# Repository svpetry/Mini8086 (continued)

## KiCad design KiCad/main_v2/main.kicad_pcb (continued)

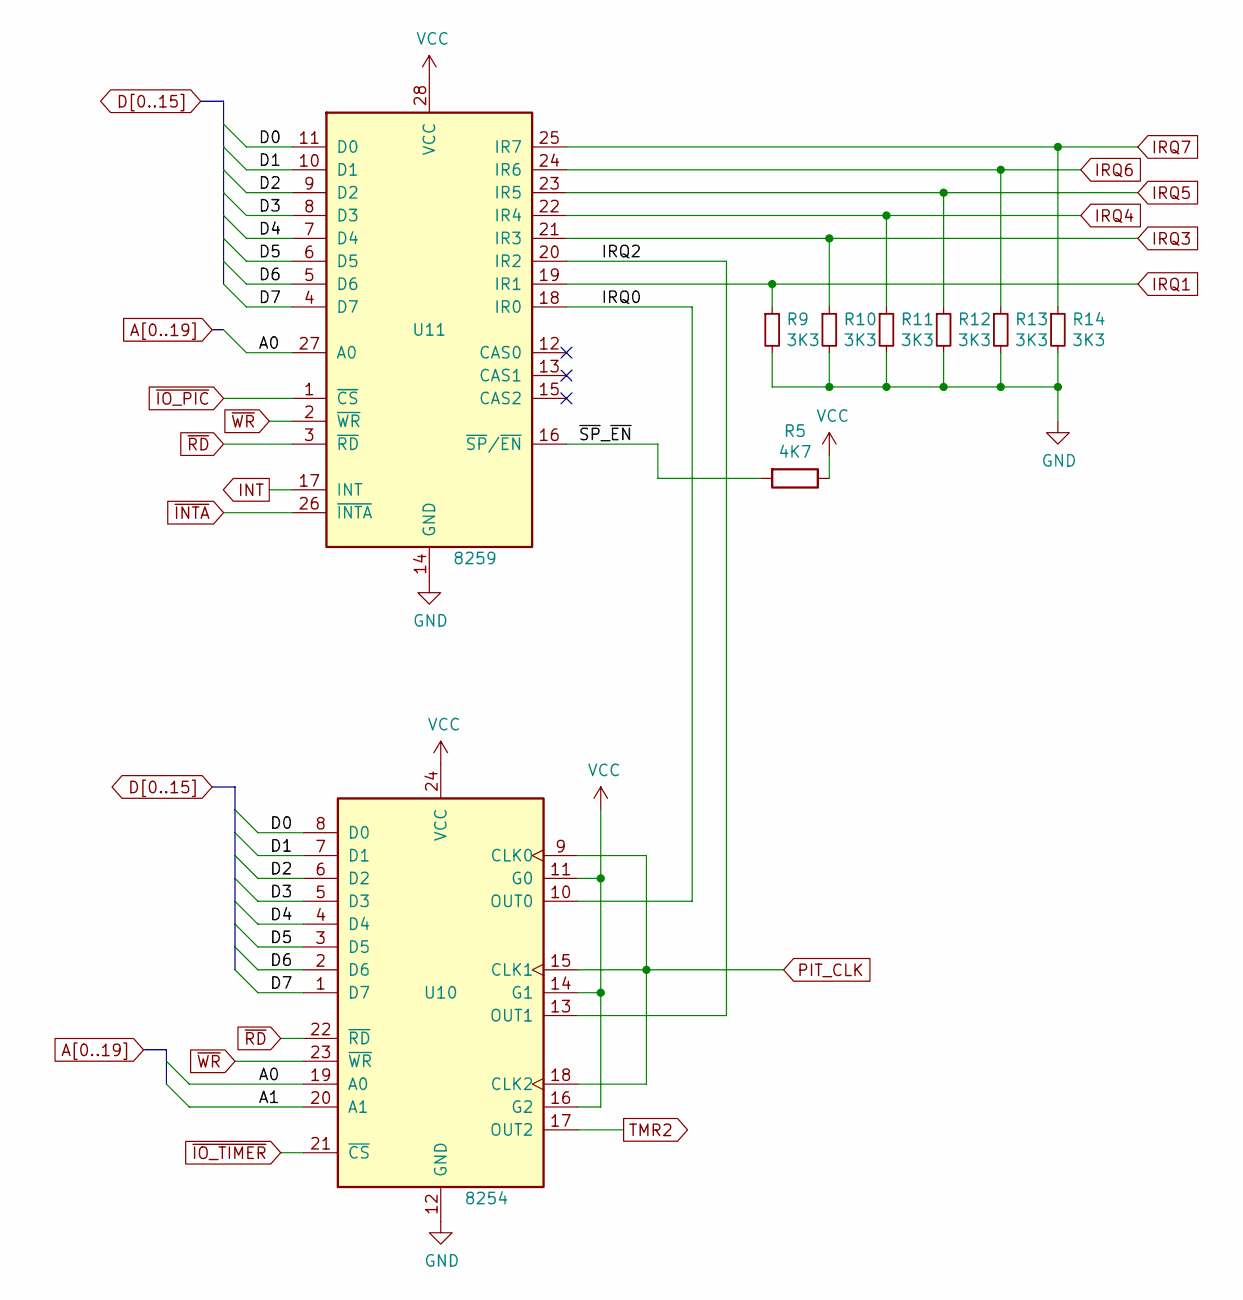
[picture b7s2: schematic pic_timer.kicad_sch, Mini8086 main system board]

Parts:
R5: 4K7; R_1206_3216Metric
R9, R10, R11, R12, R13, R14: 3K3; R_1206_3216Metric
U10: 8254; DIP-24_W15.24mm_Socket_LongPads
U11: 8259; DIP-28_W15.24mm_Socket_LongPads

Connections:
/PIC TIMER/IRQ0: U10.10 (OUT0), U11.18 (IR0)
/PIC TIMER/IRQ2: U10.13 (OUT1), U11.20 (IR2)
/PIC TIMER/~SP~_~EN: R5.2, U11.16 (~SP/~EN)
A0: U10.19 (A0), U11.27 (A0); also elsewhere on the board
A1: U10.20 (A1); also elsewhere on the board
D0: U10.8 (D0), U11.11 (D0); also elsewhere on the board
D1: U10.7 (D1), U11.10 (D1); also elsewhere on the board
D2: U10.6 (D2), U11.9 (D2); also elsewhere on the board
D3: U10.5 (D3), U11.8 (D3); also elsewhere on the board
D4: U10.4 (D4), U11.7 (D4); also elsewhere on the board
D5: U10.3 (D5), U11.6 (D5); also elsewhere on the board
D6: U10.2 (D6), U11.5 (D6); also elsewhere on the board
D7: U10.1 (D7), U11.4 (D7); also elsewhere on the board
GND: R9.2, R10.2, R11.2, R12.2, R13.2, R14.2, U10.12 (GND), U11.14 (GND); also elsewhere on the board
INT: U11.17 (INT); also elsewhere on the board
IRQ1: R9.1, U11.19 (IR1); also elsewhere on the board
IRQ3: R10.1, U11.21 (IR3); also elsewhere on the board
IRQ4: R11.1, U11.22 (IR4); also elsewhere on the board
IRQ5: R12.1, U11.23 (IR5); also elsewhere on the board
IRQ6: R13.1, U11.24 (IR6); also elsewhere on the board
IRQ7: R14.1, U11.25 (IR7); also elsewhere on the board
PIT_CLK: U10.9 (CLK0), U10.15 (CLK1), U10.18 (CLK2); also elsewhere on the board
TMR2: U10.17 (OUT2); also elsewhere on the board
VCC: R5.1, U10.11 (G0), U10.14 (G1), U10.16 (G2), U10.24 (VCC), U11.28 (VCC); also elsewhere on the board
~INTA: U11.26 (~INTA); also elsewhere on the board
~IO_PIC: U11.1 (~CS); also elsewhere on the board
~IO_TIMER: U10.21 (~CS); also elsewhere on the board
~RD: U10.22 (~RD), U11.3 (~RD); also elsewhere on the board
~WR: U10.23 (~WR), U11.2 (~WR); also elsewhere on the board

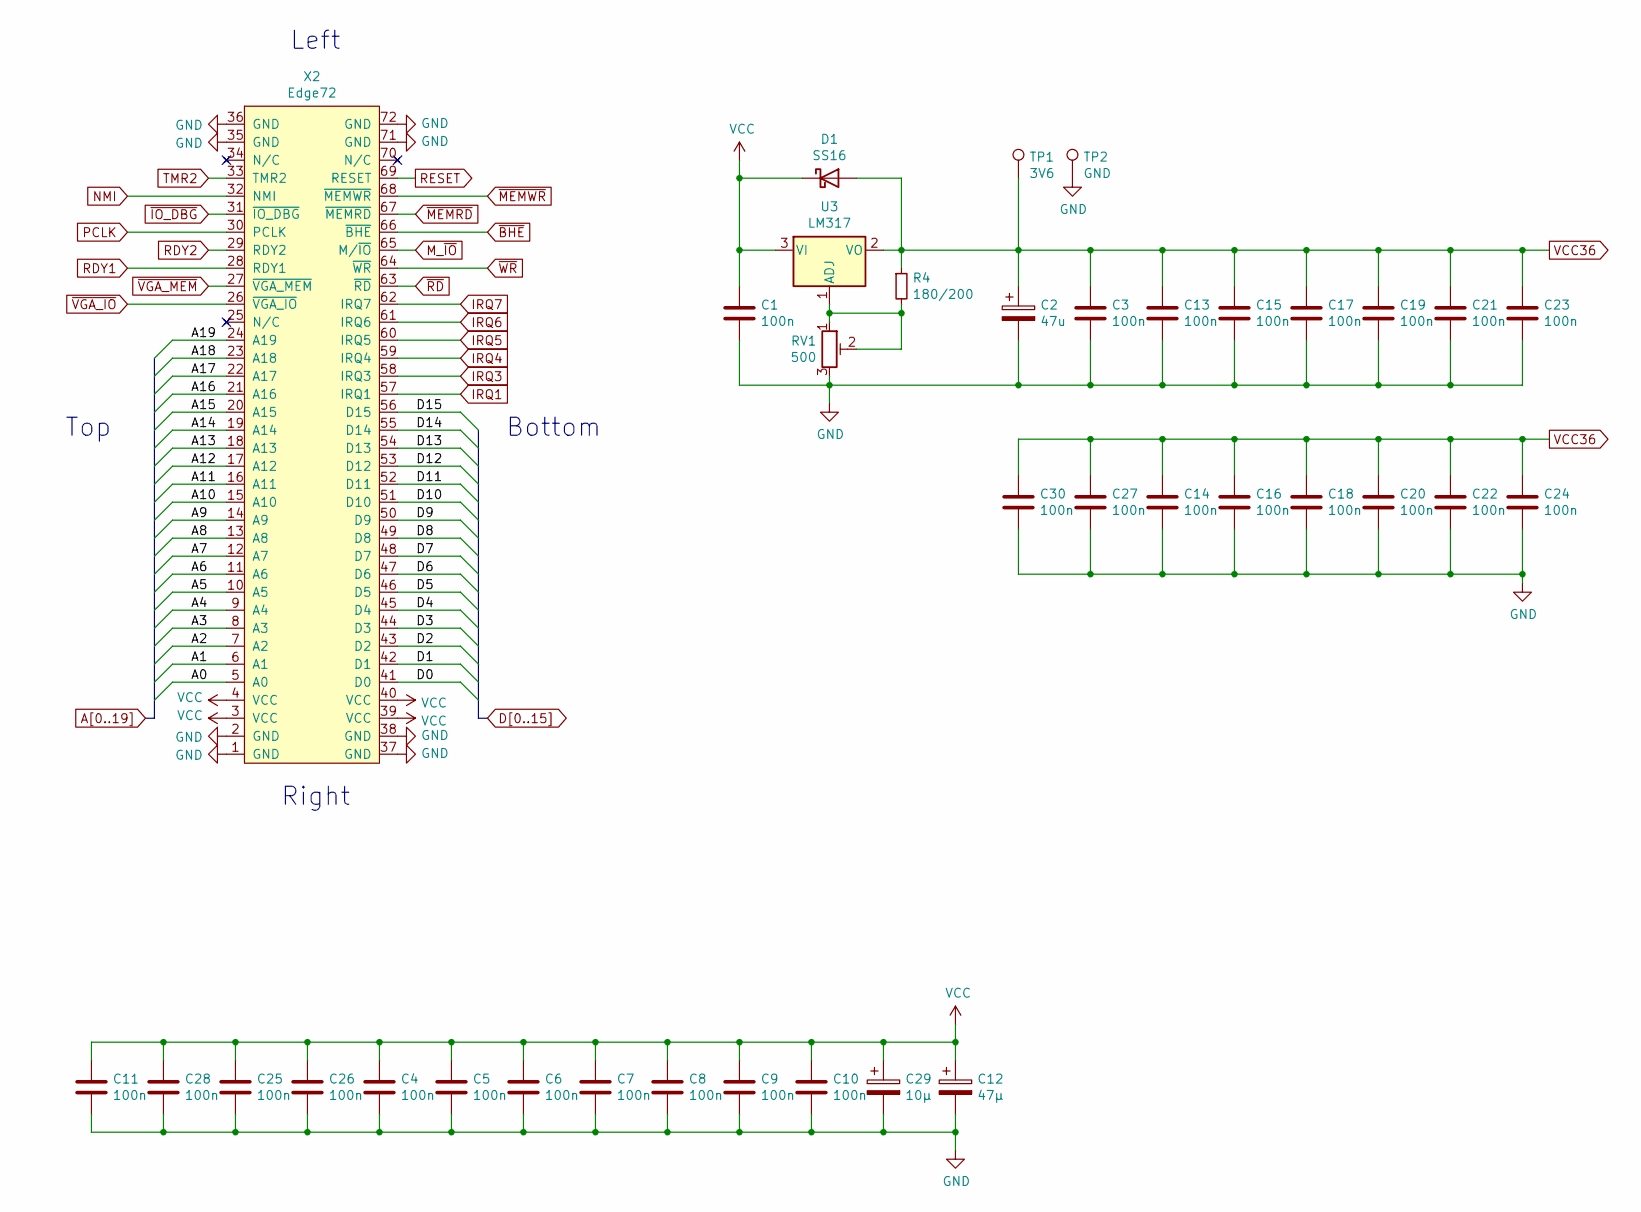
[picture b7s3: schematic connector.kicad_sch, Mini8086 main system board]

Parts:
C1, C3, C4, C5, C6, C7, C8, C9, C10, C11, C13, C14, C15, C16, C17, C18, C19, C20, C21, C22, C23, C24, C25, C26, C27, C28, C30: 100n; C_1206_3216Metric
C2: 47u; CP_Radial_D4.0mm_P2.00mm
C12: 47µ; CP_Radial_D4.0mm_P2.00mm
C29: 10µ; CP_Radial_D4.0mm_P2.00mm
D1: SS16; D_SMA
R4: 180/200; R_1206_3216Metric
RV1: 500; Potentiometer_Runtron_RM-065_Vertical
TP1: 3V6; TestPoint_Pad_D1.5mm
TP2: GND; TestPoint_Pad_D1.5mm
U3: LM317; TO-252-2
X2: Edge72; BUS_72

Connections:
A0: X2.5 (A0); also elsewhere on the board
A1: X2.6 (A1); also elsewhere on the board
A2: X2.7 (A2); also elsewhere on the board
A3: X2.8 (A3); also elsewhere on the board
A4: X2.9 (A4); also elsewhere on the board
A5: X2.10 (A5); also elsewhere on the board
A6: X2.11 (A6); also elsewhere on the board
A7: X2.12 (A7); also elsewhere on the board
A8: X2.13 (A8); also elsewhere on the board
A9: X2.14 (A9); also elsewhere on the board
A10: X2.15 (A10); also elsewhere on the board
A11: X2.16 (A11); also elsewhere on the board
A12: X2.17 (A12); also elsewhere on the board
A13: X2.18 (A13); also elsewhere on the board
A14: X2.19 (A14); also elsewhere on the board
A15: X2.20 (A15); also elsewhere on the board
A16: X2.21 (A16); also elsewhere on the board
A17: X2.22 (A17); also elsewhere on the board
A18: X2.23 (A18); also elsewhere on the board
A19: X2.24 (A19); also elsewhere on the board
D0: X2.41 (D0); also elsewhere on the board
D1: X2.42 (D1); also elsewhere on the board
D2: X2.43 (D2); also elsewhere on the board
D3: X2.44 (D3); also elsewhere on the board
D4: X2.45 (D4); also elsewhere on the board
D5: X2.46 (D5); also elsewhere on the board
D6: X2.47 (D6); also elsewhere on the board
D7: X2.48 (D7); also elsewhere on the board
D8: X2.49 (D8); also elsewhere on the board
D9: X2.50 (D9); also elsewhere on the board
D10: X2.51 (D10); also elsewhere on the board
D11: X2.52 (D11); also elsewhere on the board
D12: X2.53 (D12); also elsewhere on the board
D13: X2.54 (D13); also elsewhere on the board
D14: X2.55 (D14); also elsewhere on the board
D15: X2.56 (D15); also elsewhere on the board
GND: C1.2, C2.2, C3.2, C4.2, C5.2, C6.2, C7.2, C8.2, C9.2, C10.2, C11.2, C12.2, C13.2, C14.2, C15.2, C16.2, C17.2, C18.2, C19.2, C20.2, C21.2, C22.2, C23.2, C24.2, C25.2, C26.2, C27.2, C28.2, C29.2, C30.2, RV1.3, TP2.1, X2.1 (GND), X2.2 (GND), X2.35 (GND), X2.36 (GND), X2.37 (GND), X2.38 (GND), X2.71 (GND), X2.72 (GND); also elsewhere on the board
IRQ1: X2.57 (IRQ1); also elsewhere on the board
IRQ3: X2.58 (IRQ3); also elsewhere on the board
IRQ4: X2.59 (IRQ4); also elsewhere on the board
IRQ5: X2.60 (IRQ5); also elsewhere on the board
IRQ6: X2.61 (IRQ6); also elsewhere on the board
IRQ7: X2.62 (IRQ7); also elsewhere on the board
M_~IO: X2.65 (M/~IO); also elsewhere on the board
NMI: X2.32 (NMI); also elsewhere on the board
unnamed: R4.2, RV1.1, RV1.2, U3.1 (ADJ)
PCLK: X2.30 (PCLK); also elsewhere on the board
RDY1: X2.28 (RDY1); also elsewhere on the board
RDY2: X2.29 (RDY2); also elsewhere on the board
RESET: X2.69 (RESET); also elsewhere on the board
TMR2: X2.33 (TMR2); also elsewhere on the board
VCC: C1.1, C4.1, C5.1, C6.1, C7.1, C8.1, C9.1, C10.1, C11.1, C12.1, C25.1, C26.1, C28.1, C29.1, D1.1 (K), U3.3 (VI), X2.3 (VCC), X2.4 (VCC), X2.39 (VCC), X2.40 (VCC); also elsewhere on the board
VCC36: C2.1, C3.1, C13.1, C14.1, C15.1, C16.1, C17.1, C18.1, C19.1, C20.1, C21.1, C22.1, C23.1, C24.1, C27.1, C30.1, D1.2 (A), R4.1, TP1.1, U3.2 (VO); also elsewhere on the board
~BHE: X2.66 (~BHE); also elsewhere on the board
~IO_DBG: X2.31 (~IO_DBG); also elsewhere on the board
~MEMRD: X2.67 (~MEMRD); also elsewhere on the board
~MEMWR: X2.68 (~MEMWR); also elsewhere on the board
~RD: X2.63 (~RD); also elsewhere on the board
~VGA_IO: X2.26 (~VGA_IO); also elsewhere on the board
~VGA_MEM: X2.27 (~VGA_MEM); also elsewhere on the board
~WR: X2.64 (~WR); also elsewhere on the board

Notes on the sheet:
Top
Right
Left
Bottom

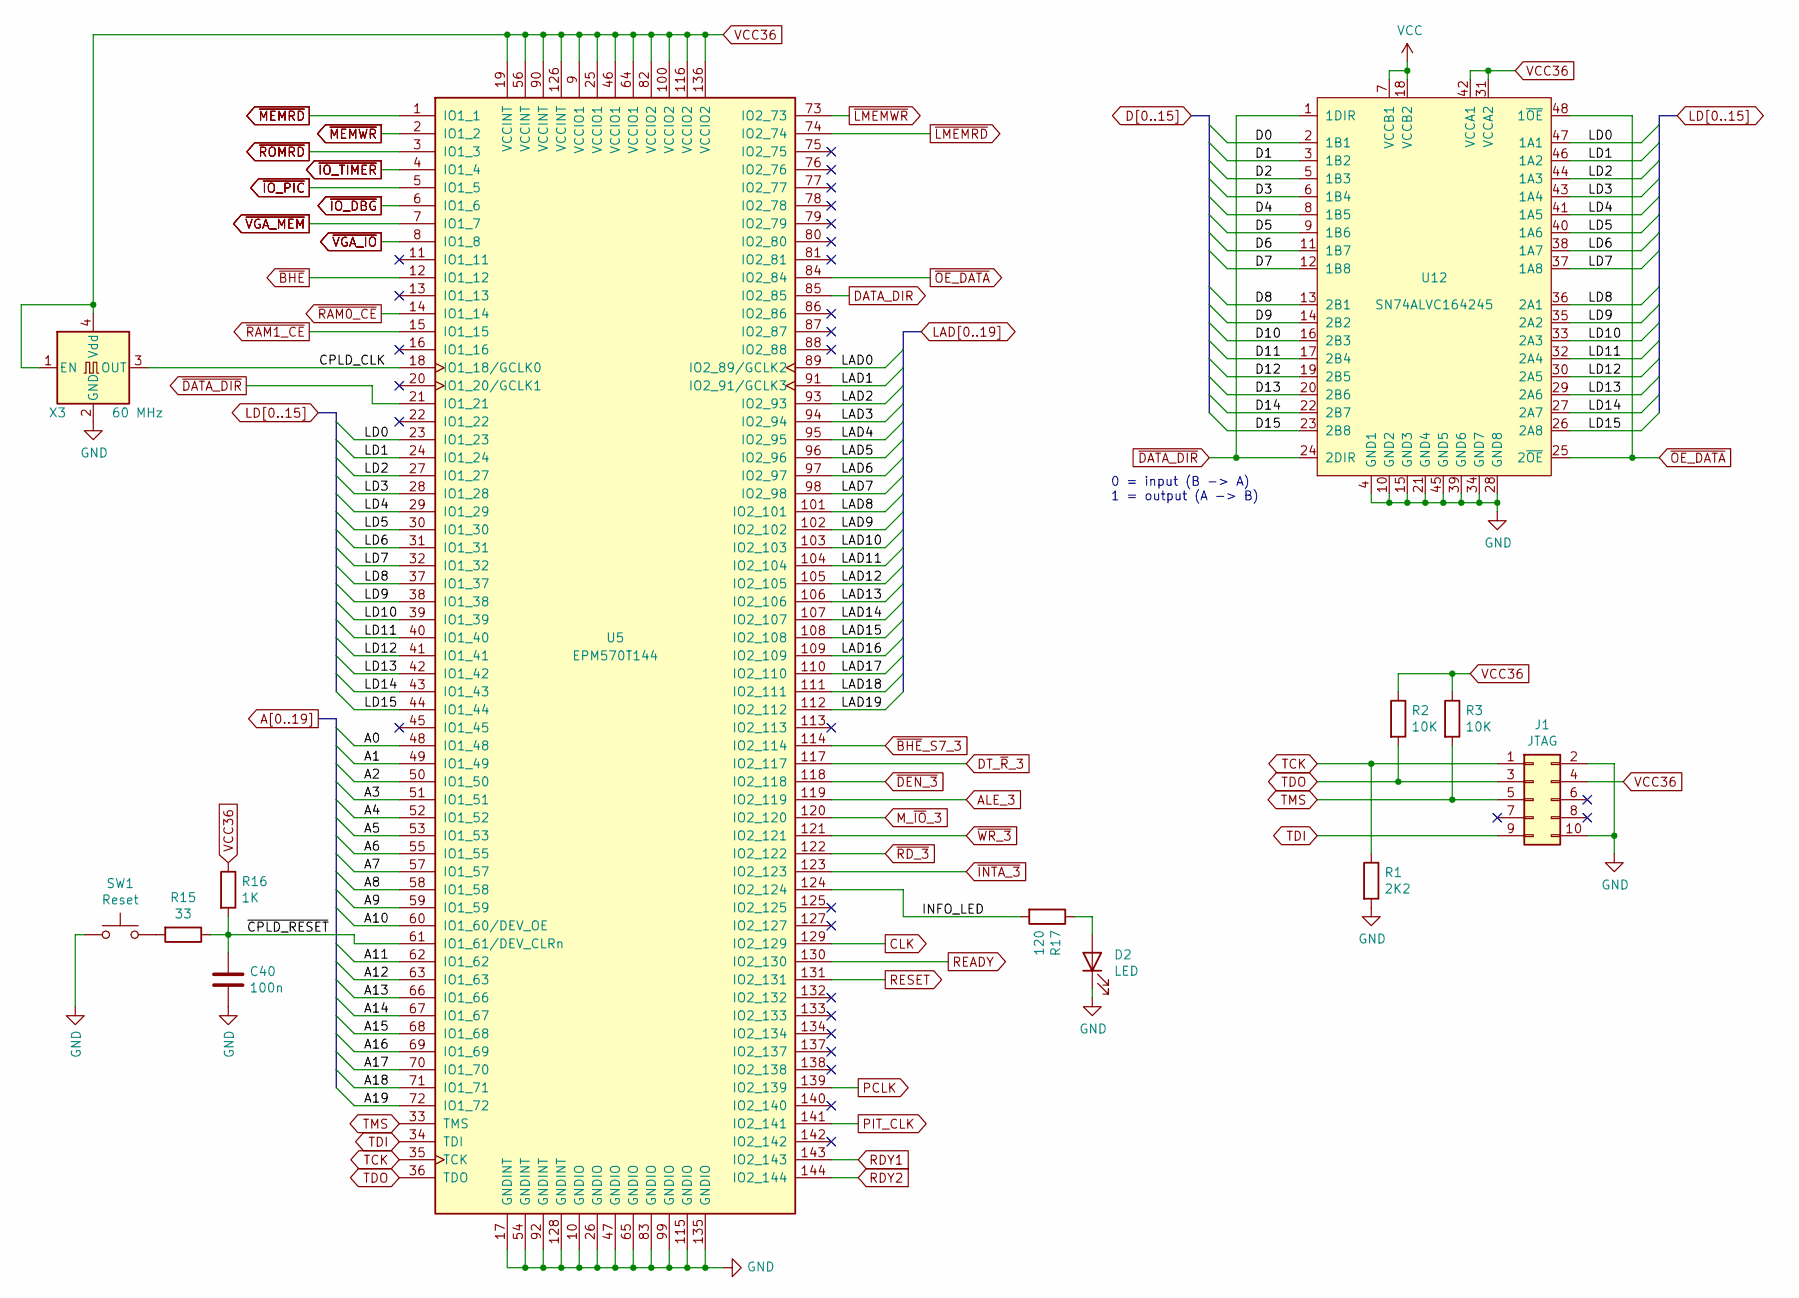
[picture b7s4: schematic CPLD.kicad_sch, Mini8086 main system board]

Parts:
C40: 100n; C_1206_3216Metric
D2: LED; LED_0805_2012Metric_Castellated
J1: JTAG; IDC-Header_2x05_P2.54mm_Vertical
R1: 2K2; R_1206_3216Metric
R2, R3: 10K; R_1206_3216Metric
R15: 33; R_1206_3216Metric
R16: 1K; R_1206_3216Metric
R17: 120; R_0805_2012Metric
SW1: Reset; SW_SPST_CK_RS282G05A3
U5: EPM570T144; LQFP-144_20x20mm_P0.5mm
U12: SN74ALVC164245; SSOP-48_7.5x15.9mm_P0.635mm
X3: 60 MHz; Oscillator_SMD_Abracon_ASV-4Pin_7.0x5.1mm

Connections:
/CPLD/CPLD_CLK: U5.18 (IO1_18/GCLK0), X3.3 (OUT)
/CPLD/INFO_LED: R17.2, U5.124 (IO2_124)
/CPLD/~CPLD_RESET: C40.1, R15.1, R16.2, U5.61 (IO1_61/DEV_CLRn)
A0: U5.48 (IO1_48); also elsewhere on the board
A1: U5.49 (IO1_49); also elsewhere on the board
A2: U5.50 (IO1_50); also elsewhere on the board
A3: U5.51 (IO1_51); also elsewhere on the board
A4: U5.52 (IO1_52); also elsewhere on the board
A5: U5.53 (IO1_53); also elsewhere on the board
A6: U5.55 (IO1_55); also elsewhere on the board
A7: U5.57 (IO1_57); also elsewhere on the board
A8: U5.58 (IO1_58); also elsewhere on the board
A9: U5.59 (IO1_59); also elsewhere on the board
A10: U5.60 (IO1_60/DEV_OE); also elsewhere on the board
A11: U5.62 (IO1_62); also elsewhere on the board
A12: U5.63 (IO1_63); also elsewhere on the board
A13: U5.66 (IO1_66); also elsewhere on the board
A14: U5.67 (IO1_67); also elsewhere on the board
A15: U5.68 (IO1_68); also elsewhere on the board
A16: U5.69 (IO1_69); also elsewhere on the board
A17: U5.70 (IO1_70); also elsewhere on the board
A18: U5.71 (IO1_71); also elsewhere on the board
A19: U5.72 (IO1_72); also elsewhere on the board
ALE_3: U5.119 (IO2_119); also elsewhere on the board
CLK: U5.129 (IO2_129); also elsewhere on the board
D0: U12.2 (1B1); also elsewhere on the board
D1: U12.3 (1B2); also elsewhere on the board
D2: U12.5 (1B3); also elsewhere on the board
D3: U12.6 (1B4); also elsewhere on the board
D4: U12.8 (1B5); also elsewhere on the board
D5: U12.9 (1B6); also elsewhere on the board
D6: U12.11 (1B7); also elsewhere on the board
D7: U12.12 (1B8); also elsewhere on the board
D8: U12.13 (2B1); also elsewhere on the board
D9: U12.14 (2B2); also elsewhere on the board
D10: U12.16 (2B3); also elsewhere on the board
D11: U12.17 (2B4); also elsewhere on the board
D12: U12.19 (2B5); also elsewhere on the board
D13: U12.20 (2B6); also elsewhere on the board
D14: U12.22 (2B7); also elsewhere on the board
D15: U12.23 (2B8); also elsewhere on the board
DATA_DIR: U5.85 (IO2_85); also elsewhere on the board
DT_~R~_3: U5.117 (IO2_117); also elsewhere on the board
GND: C40.2, D2.1 (K), J1.2, J1.10, R1.2, SW1.1, U5.10 (GNDIO), U5.17 (GNDINT), U5.26 (GNDIO), U5.47 (GNDIO), U5.54 (GNDINT), U5.65 (GNDIO), U5.83 (GNDIO), U5.92 (GNDINT), U5.99 (GNDIO), U5.115 (GNDIO), U5.128 (GNDINT), U5.135 (GNDIO), U12.4 (GND1), U12.10 (GND2), U12.15 (GND3), U12.21 (GND4), U12.28 (GND8), U12.34 (GND7), U12.39 (GND6), U12.45 (GND5), X3.2 (GND); also elsewhere on the board
LAD0: U5.89 (IO2_89/GCLK2); also elsewhere on the board
LAD1: U5.91 (IO2_91/GCLK3); also elsewhere on the board
LAD2: U5.93 (IO2_93); also elsewhere on the board
LAD3: U5.94 (IO2_94); also elsewhere on the board
LAD4: U5.95 (IO2_95); also elsewhere on the board
LAD5: U5.96 (IO2_96); also elsewhere on the board
LAD6: U5.97 (IO2_97); also elsewhere on the board
LAD7: U5.98 (IO2_98); also elsewhere on the board
LAD8: U5.101 (IO2_101); also elsewhere on the board
LAD9: U5.102 (IO2_102); also elsewhere on the board
LAD10: U5.103 (IO2_103); also elsewhere on the board
LAD11: U5.104 (IO2_104); also elsewhere on the board
LAD12: U5.105 (IO2_105); also elsewhere on the board
LAD13: U5.106 (IO2_106); also elsewhere on the board
LAD14: U5.107 (IO2_107); also elsewhere on the board
LAD15: U5.108 (IO2_108); also elsewhere on the board
LAD16: U5.109 (IO2_109); also elsewhere on the board
LAD17: U5.110 (IO2_110); also elsewhere on the board
LAD18: U5.111 (IO2_111); also elsewhere on the board
LAD19: U5.112 (IO2_112); also elsewhere on the board
LD0: U5.23 (IO1_23), U12.47 (1A1); also elsewhere on the board
LD1: U5.24 (IO1_24), U12.46 (1A2); also elsewhere on the board
LD2: U5.27 (IO1_27), U12.44 (1A3); also elsewhere on the board
LD3: U5.28 (IO1_28), U12.43 (1A4); also elsewhere on the board
LD4: U5.29 (IO1_29), U12.41 (1A5); also elsewhere on the board
LD5: U5.30 (IO1_30), U12.40 (1A6); also elsewhere on the board
LD6: U5.31 (IO1_31), U12.38 (1A7); also elsewhere on the board
LD7: U5.32 (IO1_32), U12.37 (1A8); also elsewhere on the board
LD8: U5.37 (IO1_37), U12.36 (2A1); also elsewhere on the board
LD9: U5.38 (IO1_38), U12.35 (2A2); also elsewhere on the board
LD10: U5.39 (IO1_39), U12.33 (2A3); also elsewhere on the board
LD11: U5.40 (IO1_40), U12.32 (2A4); also elsewhere on the board
LD12: U5.41 (IO1_41), U12.30 (2A5); also elsewhere on the board
LD13: U5.42 (IO1_42), U12.29 (2A6); also elsewhere on the board
LD14: U5.43 (IO1_43), U12.27 (2A7); also elsewhere on the board
LD15: U5.44 (IO1_44), U12.26 (2A8); also elsewhere on the board
M_~IO~_3: U5.120 (IO2_120); also elsewhere on the board
unnamed: D2.2 (A), R17.1
unnamed: R15.2, SW1.2
PCLK: U5.139 (IO2_139); also elsewhere on the board
PIT_CLK: U5.141 (IO2_141); also elsewhere on the board
RDY1: U5.143 (IO2_143); also elsewhere on the board
RDY2: U5.144 (IO2_144); also elsewhere on the board
READY: U5.130 (IO2_130); also elsewhere on the board
RESET: U5.131 (IO2_131); also elsewhere on the board
TCK: J1.1, R1.1, U5.35 (TCK)
TDI: J1.9, U5.34 (TDI)
TDO: J1.3, R2.2, U5.36 (TDO)
TMS: J1.5, R3.2, U5.33 (TMS)
VCC: U12.7 (VCCB1), U12.18 (VCCB2); also elsewhere on the board
VCC36: J1.4, R2.1, R3.1, R16.1, U5.9 (VCCIO1), U5.19 (VCCINT), U5.25 (VCCIO1), U5.46 (VCCIO1), U5.56 (VCCINT), U5.64 (VCCIO1), U5.82 (VCCIO2), U5.90 (VCCINT), U5.100 (VCCIO2), U5.116 (VCCIO2), U5.126 (VCCINT), U5.136 (VCCIO2), U12.31 (VCCA2), U12.42 (VCCA1), X3.1 (EN), X3.4 (Vdd); also elsewhere on the board
~BHE: U5.12 (IO1_12); also elsewhere on the board
~BHE~_S7_3: U5.114 (IO2_114); also elsewhere on the board
~DATA_DIR: U5.21 (IO1_21), U12.1 (1DIR), U12.24 (2DIR)
~DEN_3: U5.118 (IO2_118); also elsewhere on the board
~INTA_3: U5.123 (IO2_123); also elsewhere on the board
~IO_DBG: U5.6 (IO1_6); also elsewhere on the board
~IO_PIC: U5.5 (IO1_5); also elsewhere on the board
~IO_TIMER: U5.4 (IO1_4); also elsewhere on the board
~LMEMRD: U5.74 (IO2_74); also elsewhere on the board
~LMEMWR: U5.73 (IO2_73); also elsewhere on the board
~MEMRD: U5.1 (IO1_1); also elsewhere on the board
~MEMWR: U5.2 (IO1_2); also elsewhere on the board
~OE_DATA: U5.84 (IO2_84), U12.25 (2~OE), U12.48 (1~OE)
~RAM0_CE: U5.14 (IO1_14); also elsewhere on the board
~RAM1_CE: U5.15 (IO1_15); also elsewhere on the board
~RD_3: U5.122 (IO2_122); also elsewhere on the board
~ROMRD: U5.3 (IO1_3); also elsewhere on the board
~VGA_IO: U5.8 (IO1_8); also elsewhere on the board
~VGA_MEM: U5.7 (IO1_7); also elsewhere on the board
~WR_3: U5.121 (IO2_121); also elsewhere on the board

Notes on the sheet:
0 = input (B -> A) 1 = output (A -> B)

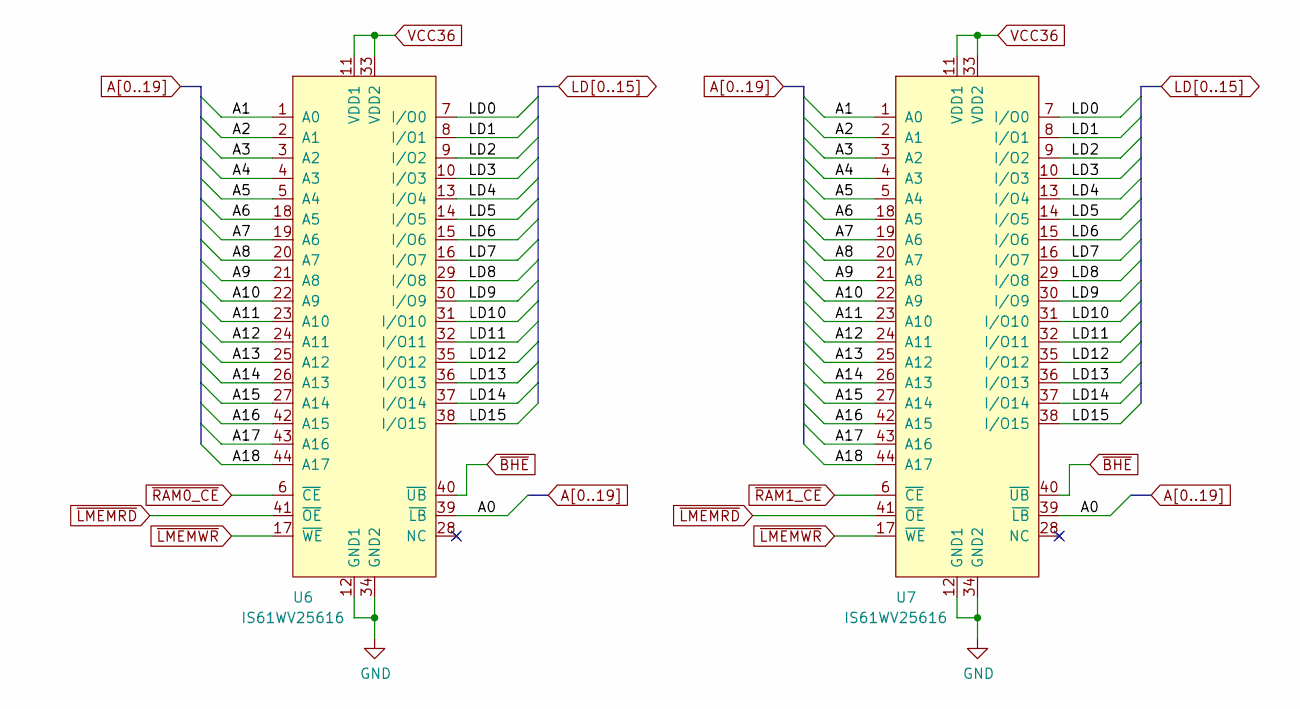
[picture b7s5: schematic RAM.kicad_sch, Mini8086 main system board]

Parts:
U6, U7: IS61WV25616; TSOP-II-44_10.16x18.41mm_P0.8mm

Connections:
A0: U6.39 (~LB), U7.39 (~LB); also elsewhere on the board
A1: U6.1 (A0), U7.1 (A0); also elsewhere on the board
A2: U6.2 (A1), U7.2 (A1); also elsewhere on the board
A3: U6.3 (A2), U7.3 (A2); also elsewhere on the board
A4: U6.4 (A3), U7.4 (A3); also elsewhere on the board
A5: U6.5 (A4), U7.5 (A4); also elsewhere on the board
A6: U6.18 (A5), U7.18 (A5); also elsewhere on the board
A7: U6.19 (A6), U7.19 (A6); also elsewhere on the board
A8: U6.20 (A7), U7.20 (A7); also elsewhere on the board
A9: U6.21 (A8), U7.21 (A8); also elsewhere on the board
A10: U6.22 (A9), U7.22 (A9); also elsewhere on the board
A11: U6.23 (A10), U7.23 (A10); also elsewhere on the board
A12: U6.24 (A11), U7.24 (A11); also elsewhere on the board
A13: U6.25 (A12), U7.25 (A12); also elsewhere on the board
A14: U6.26 (A13), U7.26 (A13); also elsewhere on the board
A15: U6.27 (A14), U7.27 (A14); also elsewhere on the board
A16: U6.42 (A15), U7.42 (A15); also elsewhere on the board
A17: U6.43 (A16), U7.43 (A16); also elsewhere on the board
A18: U6.44 (A17), U7.44 (A17); also elsewhere on the board
GND: U6.12 (GND1), U6.34 (GND2), U7.12 (GND1), U7.34 (GND2); also elsewhere on the board
LD0: U6.7 (I/O0), U7.7 (I/O0); also elsewhere on the board
LD1: U6.8 (I/O1), U7.8 (I/O1); also elsewhere on the board
LD2: U6.9 (I/O2), U7.9 (I/O2); also elsewhere on the board
LD3: U6.10 (I/O3), U7.10 (I/O3); also elsewhere on the board
LD4: U6.13 (I/O4), U7.13 (I/O4); also elsewhere on the board
LD5: U6.14 (I/O5), U7.14 (I/O5); also elsewhere on the board
LD6: U6.15 (I/O6), U7.15 (I/O6); also elsewhere on the board
LD7: U6.16 (I/O7), U7.16 (I/O7); also elsewhere on the board
LD8: U6.29 (I/O8), U7.29 (I/O8); also elsewhere on the board
LD9: U6.30 (I/O9), U7.30 (I/O9); also elsewhere on the board
LD10: U6.31 (I/O10), U7.31 (I/O10); also elsewhere on the board
LD11: U6.32 (I/O11), U7.32 (I/O11); also elsewhere on the board
LD12: U6.35 (I/O12), U7.35 (I/O12); also elsewhere on the board
LD13: U6.36 (I/O13), U7.36 (I/O13); also elsewhere on the board
LD14: U6.37 (I/O14), U7.37 (I/O14); also elsewhere on the board
LD15: U6.38 (I/O15), U7.38 (I/O15); also elsewhere on the board
VCC36: U6.11 (VDD1), U6.33 (VDD2), U7.11 (VDD1), U7.33 (VDD2); also elsewhere on the board
~BHE: U6.40 (~UB), U7.40 (~UB); also elsewhere on the board
~LMEMRD: U6.41 (~OE), U7.41 (~OE); also elsewhere on the board
~LMEMWR: U6.17 (~WE), U7.17 (~WE); also elsewhere on the board
~RAM0_CE: U6.6 (~CE); also elsewhere on the board
~RAM1_CE: U7.6 (~CE); also elsewhere on the board

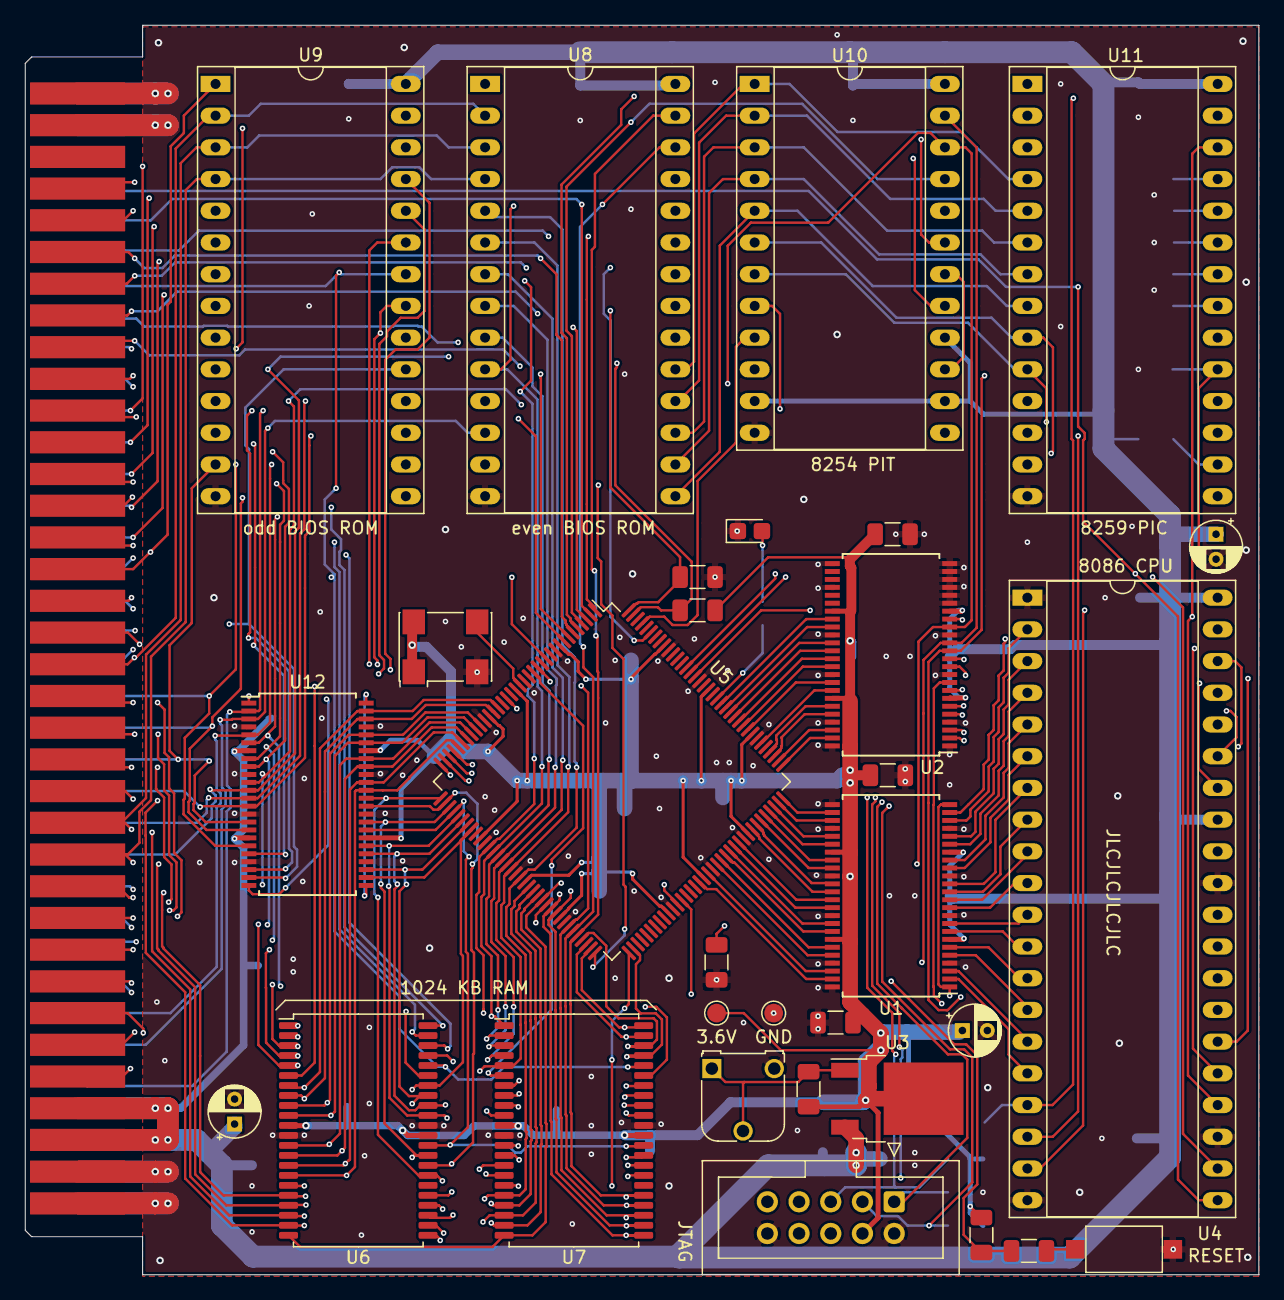
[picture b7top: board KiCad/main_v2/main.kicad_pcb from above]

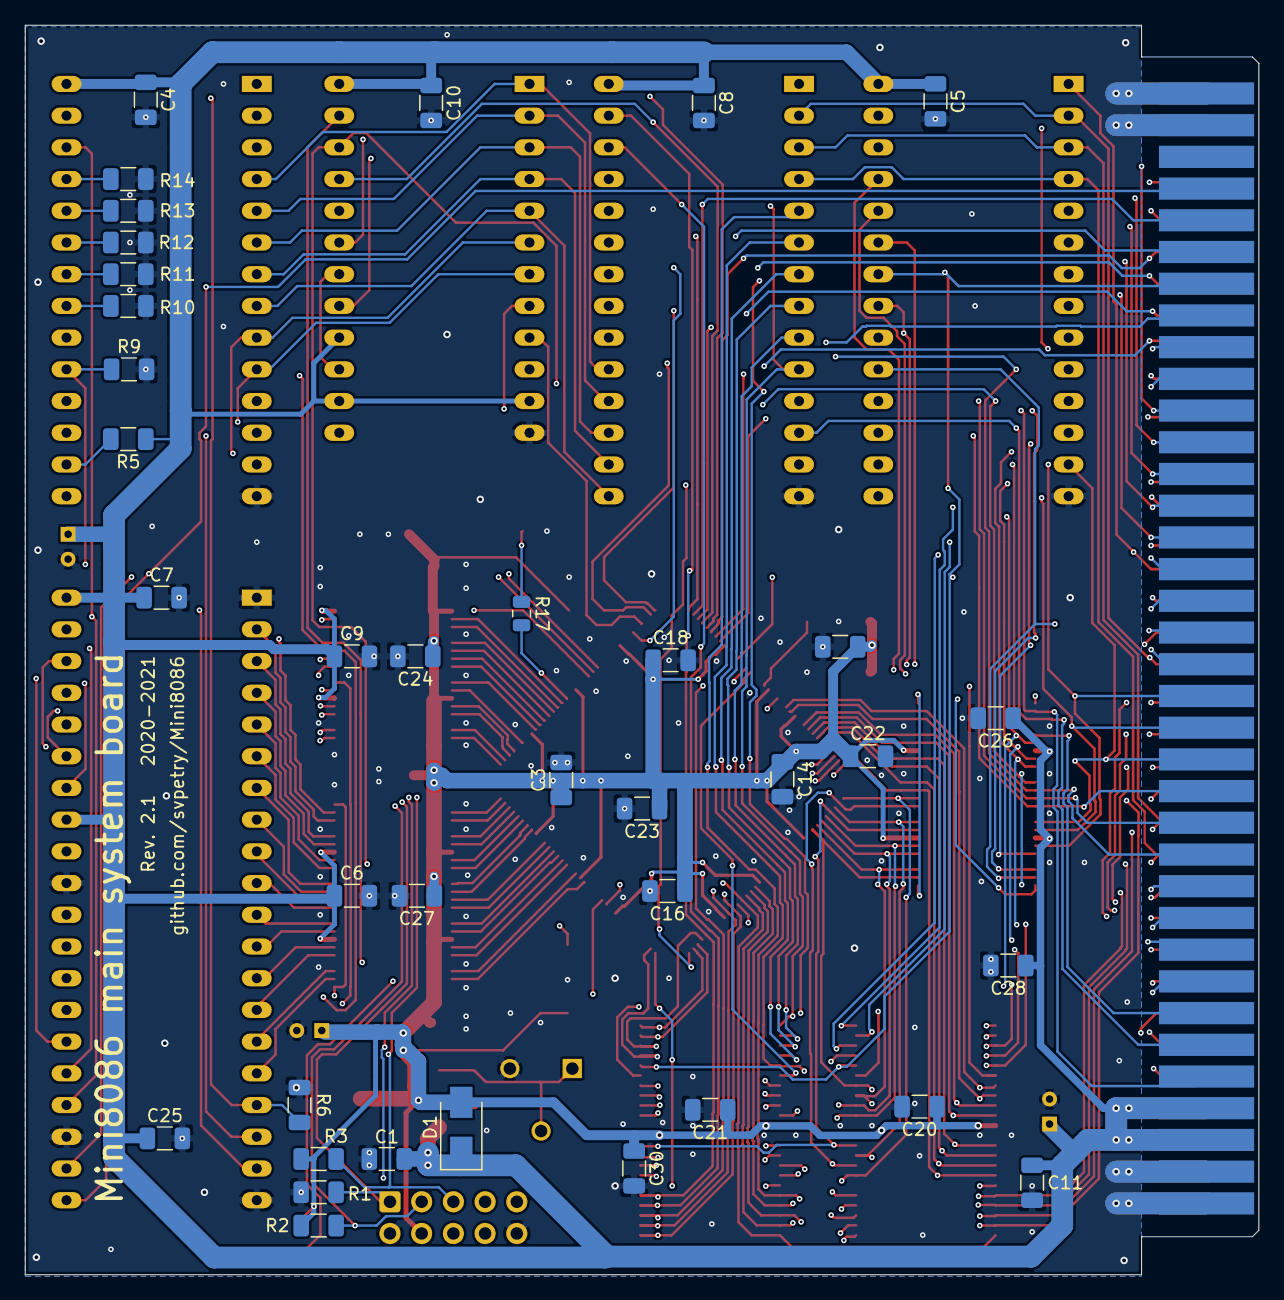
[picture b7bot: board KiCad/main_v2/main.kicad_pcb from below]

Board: 4 copper layers, 98.8 x 100.1 mm, 69 parts (37 on the bottom side), 156 nets.

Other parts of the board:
U8, U9: 27C512; DIP-28_W15.24mm_Socket_LongPads

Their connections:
A0: U8.22; also elsewhere on the board
A1: U8.10, U9.10; also elsewhere on the board
A2: U8.9, U9.9; also elsewhere on the board
A3: U8.8, U9.8; also elsewhere on the board
A4: U8.7, U9.7; also elsewhere on the board
A5: U8.6, U9.6; also elsewhere on the board
A6: U8.5, U9.5; also elsewhere on the board
A7: U8.4, U9.4; also elsewhere on the board
A8: U8.3, U9.3; also elsewhere on the board
A9: U8.25, U9.25; also elsewhere on the board
A10: U8.24, U9.24; also elsewhere on the board
A11: U8.21, U9.21; also elsewhere on the board
A12: U8.23, U9.23; also elsewhere on the board
A13: U8.2, U9.2; also elsewhere on the board
A14: U8.26, U9.26; also elsewhere on the board
A15: U8.27, U9.27; also elsewhere on the board
A16: U8.1, U9.1; also elsewhere on the board
D0: U8.11; also elsewhere on the board
D1: U8.12; also elsewhere on the board
D2: U8.13; also elsewhere on the board
D3: U8.15; also elsewhere on the board
D4: U8.16; also elsewhere on the board
D5: U8.17; also elsewhere on the board
D6: U8.18; also elsewhere on the board
D7: U8.19; also elsewhere on the board
D8: U9.11; also elsewhere on the board
D9: U9.12; also elsewhere on the board
D10: U9.13; also elsewhere on the board
D11: U9.15; also elsewhere on the board
D12: U9.16; also elsewhere on the board
D13: U9.17; also elsewhere on the board
D14: U9.18; also elsewhere on the board
D15: U9.19; also elsewhere on the board
GND: U8.14, U9.14; also elsewhere on the board
VCC: U8.28, U9.28; also elsewhere on the board
~BHE: U9.22; also elsewhere on the board
~ROMRD: U8.20, U9.20; also elsewhere on the board
